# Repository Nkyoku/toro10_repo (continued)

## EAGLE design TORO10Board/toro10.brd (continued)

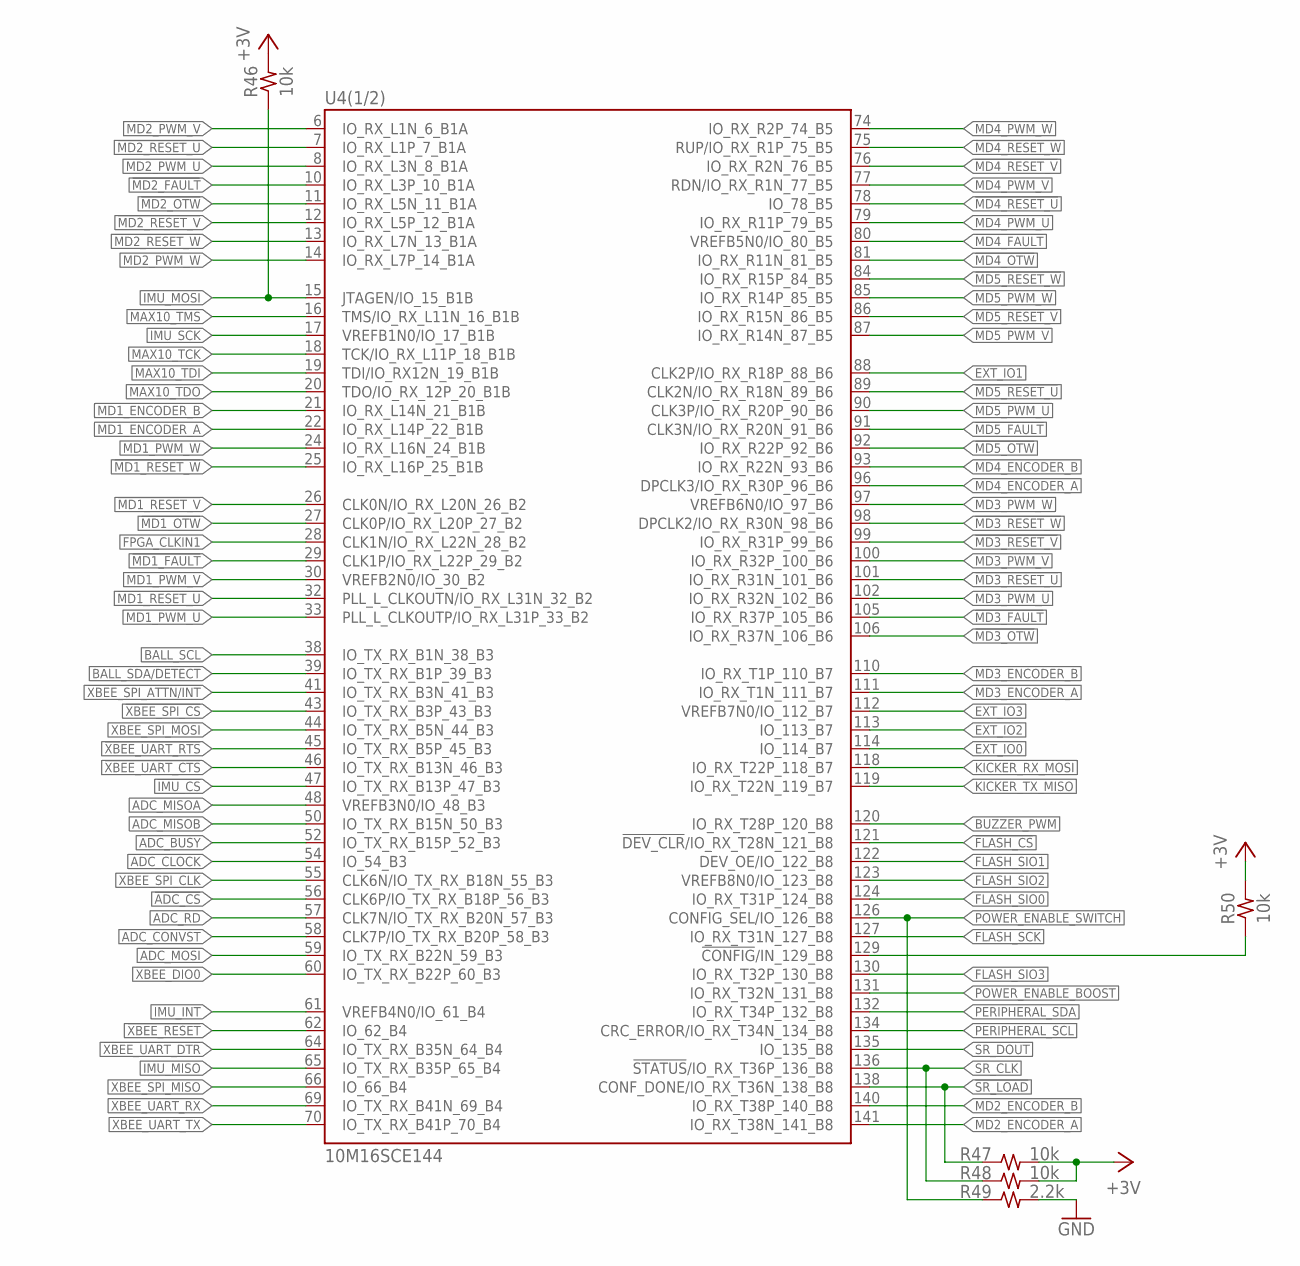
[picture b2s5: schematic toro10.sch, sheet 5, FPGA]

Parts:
R46, R47, R48, R50: 10k; 1608
R49: 2.2k; 1608
U4: 10M16SCE144; QFP144-0.5-PAD

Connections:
!ADC_CS: U4.56 (CLK6P/IO_TX_RX_B18P_56_B3); also elsewhere on the board
!FLASH_CS: U4.121 (!DEV_CLR!/IO_RX_T28N_121_B8); also elsewhere on the board
!IMU_CS: U4.47 (IO_TX_RX_B13P_47_B3); also elsewhere on the board
!MAX10_CONFIG: R50.1, U4.129 (!CONFIG!/IN_129_B8)
!MD1_FAULT: U4.29 (CLK1P/IO_RX_L22P_29_B2); also elsewhere on the board
!MD1_OTW: U4.27 (CLK0P/IO_RX_L20P_27_B2); also elsewhere on the board
!MD1_RESET_U: U4.32 (PLL_L_CLKOUTN/IO_RX_L31N_32_B2); also elsewhere on the board
!MD1_RESET_V: U4.26 (CLK0N/IO_RX_L20N_26_B2); also elsewhere on the board
!MD1_RESET_W: U4.25 (IO_RX_L16P_25_B1B); also elsewhere on the board
!MD2_FAULT: U4.10 (IO_RX_L3P_10_B1A); also elsewhere on the board
!MD2_OTW: U4.11 (IO_RX_L5N_11_B1A); also elsewhere on the board
!MD2_RESET_U: U4.7 (IO_RX_L1P_7_B1A); also elsewhere on the board
!MD2_RESET_V: U4.12 (IO_RX_L5P_12_B1A); also elsewhere on the board
!MD2_RESET_W: U4.13 (IO_RX_L7N_13_B1A); also elsewhere on the board
!MD3_FAULT: U4.105 (IO_RX_R37P_105_B6); also elsewhere on the board
!MD3_OTW: U4.106 (IO_RX_R37N_106_B6); also elsewhere on the board
!MD3_RESET_U: U4.101 (IO_RX_R31N_101_B6); also elsewhere on the board
!MD3_RESET_V: U4.99 (IO_RX_R31P_99_B6); also elsewhere on the board
!MD3_RESET_W: U4.98 (DPCLK2/IO_RX_R30N_98_B6); also elsewhere on the board
!MD4_FAULT: U4.80 (VREFB5N0/IO_80_B5); also elsewhere on the board
!MD4_OTW: U4.81 (IO_RX_R11N_81_B5); also elsewhere on the board
!MD4_RESET_U: U4.78 (IO_78_B5); also elsewhere on the board
!MD4_RESET_V: U4.76 (IO_RX_R2N_76_B5); also elsewhere on the board
!MD4_RESET_W: U4.75 (RUP/IO_RX_R1P_75_B5); also elsewhere on the board
!MD5_FAULT: U4.91 (CLK3N/IO_RX_R20N_91_B6); also elsewhere on the board
!MD5_OTW: U4.92 (IO_RX_R22P_92_B6); also elsewhere on the board
!MD5_RESET_U: U4.89 (CLK2N/IO_RX_R18N_89_B6); also elsewhere on the board
!MD5_RESET_V: U4.86 (IO_RX_R15N_86_B5); also elsewhere on the board
!MD5_RESET_W: U4.84 (IO_RX_R15P_84_B5); also elsewhere on the board
!SR_LOAD: R47.1, U4.138 (CONF_DONE/IO_RX_T36N_138_B8); also elsewhere on the board
!XBEE_RESET: U4.62 (IO_62_B4); also elsewhere on the board
!XBEE_SPI_ATTN/INT: U4.41 (IO_TX_RX_B3N_41_B3); also elsewhere on the board
!XBEE_SPI_CS: U4.43 (IO_TX_RX_B3P_43_B3); also elsewhere on the board
!XBEE_UART_CTS: U4.46 (IO_TX_RX_B13N_46_B3); also elsewhere on the board
!XBEE_UART_DTR: U4.64 (IO_TX_RX_B35N_64_B4); also elsewhere on the board
!XBEE_UART_RTS: U4.45 (IO_TX_RX_B5P_45_B3); also elsewhere on the board
+3V: R46.2, R47.2, R48.2, R50.2; also elsewhere on the board
ADC_BUSY: U4.52 (IO_TX_RX_B15P_52_B3); also elsewhere on the board
ADC_CLOCK: U4.54 (IO_54_B3); also elsewhere on the board
ADC_CONVST: U4.58 (CLK7P/IO_TX_RX_B20P_58_B3); also elsewhere on the board
ADC_MISOA: U4.48 (VREFB3N0/IO_48_B3); also elsewhere on the board
ADC_MISOB: U4.50 (IO_TX_RX_B15N_50_B3); also elsewhere on the board
ADC_MOSI: U4.59 (IO_TX_RX_B22N_59_B3); also elsewhere on the board
ADC_RD: U4.57 (CLK7N/IO_TX_RX_B20N_57_B3); also elsewhere on the board
BALL_SCL: U4.38 (IO_TX_RX_B1N_38_B3); also elsewhere on the board
BALL_SDA/DETECT: U4.39 (IO_TX_RX_B1P_39_B3); also elsewhere on the board
BUZZER_PWM: U4.120 (IO_RX_T28P_120_B8); also elsewhere on the board
EXT_IO0: U4.114 (IO_114_B7); also elsewhere on the board
EXT_IO1: U4.88 (CLK2P/IO_RX_R18P_88_B6); also elsewhere on the board
EXT_IO2: U4.113 (IO_113_B7); also elsewhere on the board
EXT_IO3: U4.112 (VREFB7N0/IO_112_B7); also elsewhere on the board
FLASH_SCK: U4.127 (IO_RX_T31N_127_B8); also elsewhere on the board
FLASH_SIO0: U4.124 (IO_RX_T31P_124_B8); also elsewhere on the board
FLASH_SIO1: U4.122 (DEV_OE/IO_122_B8); also elsewhere on the board
FLASH_SIO2: U4.123 (VREFB8N0/IO_123_B8); also elsewhere on the board
FLASH_SIO3: U4.130 (IO_RX_T32P_130_B8); also elsewhere on the board
FPGA_CLKIN1: U4.28 (CLK1N/IO_RX_L22N_28_B2); also elsewhere on the board
GND: R49.2; also elsewhere on the board
IMU_INT: U4.61 (VREFB4N0/IO_61_B4); also elsewhere on the board
IMU_MISO: U4.65 (IO_TX_RX_B35P_65_B4); also elsewhere on the board
IMU_MOSI: R46.1, U4.15 (JTAGEN/IO_15_B1B); also elsewhere on the board
IMU_SCK: U4.17 (VREFB1N0/IO_17_B1B); also elsewhere on the board
KICKER_RX_MOSI: U4.118 (IO_RX_T22P_118_B7); also elsewhere on the board
KICKER_TX_MISO: U4.119 (IO_RX_T22N_119_B7); also elsewhere on the board
MAX10_TCK: U4.18 (TCK/IO_RX_L11P_18_B1B); also elsewhere on the board
MAX10_TDI: U4.19 (TDI/IO_RX12N_19_B1B); also elsewhere on the board
MAX10_TDO: U4.20 (TDO/IO_RX_12P_20_B1B); also elsewhere on the board
MAX10_TMS: U4.16 (TMS/IO_RX_L11N_16_B1B); also elsewhere on the board
MD1_ENCODER_A: U4.22 (IO_RX_L14P_22_B1B); also elsewhere on the board
MD1_ENCODER_B: U4.21 (IO_RX_L14N_21_B1B); also elsewhere on the board
MD1_PWM_U: U4.33 (PLL_L_CLKOUTP/IO_RX_L31P_33_B2); also elsewhere on the board
MD1_PWM_V: U4.30 (VREFB2N0/IO_30_B2); also elsewhere on the board
MD1_PWM_W: U4.24 (IO_RX_L16N_24_B1B); also elsewhere on the board
MD2_ENCODER_A: U4.141 (IO_RX_T38N_141_B8); also elsewhere on the board
MD2_ENCODER_B: U4.140 (IO_RX_T38P_140_B8); also elsewhere on the board
MD2_PWM_U: U4.8 (IO_RX_L3N_8_B1A); also elsewhere on the board
MD2_PWM_V: U4.6 (IO_RX_L1N_6_B1A); also elsewhere on the board
MD2_PWM_W: U4.14 (IO_RX_L7P_14_B1A); also elsewhere on the board
MD3_ENCODER_A: U4.111 (IO_RX_T1N_111_B7); also elsewhere on the board
MD3_ENCODER_B: U4.110 (IO_RX_T1P_110_B7); also elsewhere on the board
MD3_PWM_U: U4.102 (IO_RX_R32N_102_B6); also elsewhere on the board
MD3_PWM_V: U4.100 (IO_RX_R32P_100_B6); also elsewhere on the board
MD3_PWM_W: U4.97 (VREFB6N0/IO_97_B6); also elsewhere on the board
MD4_ENCODER_A: U4.96 (DPCLK3/IO_RX_R30P_96_B6); also elsewhere on the board
MD4_ENCODER_B: U4.93 (IO_RX_R22N_93_B6); also elsewhere on the board
MD4_PWM_U: U4.79 (IO_RX_R11P_79_B5); also elsewhere on the board
MD4_PWM_V: U4.77 (RDN/IO_RX_R1N_77_B5); also elsewhere on the board
MD4_PWM_W: U4.74 (IO_RX_R2P_74_B5); also elsewhere on the board
MD5_PWM_U: U4.90 (CLK3P/IO_RX_R20P_90_B6); also elsewhere on the board
MD5_PWM_V: U4.87 (IO_RX_R14N_87_B5); also elsewhere on the board
MD5_PWM_W: U4.85 (IO_RX_R14P_85_B5); also elsewhere on the board
PERIPHERAL_SCL: U4.134 (CRC_ERROR/IO_RX_T34N_134_B8); also elsewhere on the board
PERIPHERAL_SDA: U4.132 (IO_RX_T34P_132_B8); also elsewhere on the board
POWER_ENABLE_BOOST: U4.131 (IO_RX_T32N_131_B8); also elsewhere on the board
POWER_ENABLE_SWITCH: R49.1, U4.126 (CONFIG_SEL/IO_126_B8); also elsewhere on the board
SR_CLK: R48.1, U4.136 (!STATUS!/IO_RX_T36P_136_B8); also elsewhere on the board
SR_DOUT: U4.135 (IO_135_B8); also elsewhere on the board
XBEE_DIO0: U4.60 (IO_TX_RX_B22P_60_B3); also elsewhere on the board
XBEE_SPI_CLK: U4.55 (CLK6N/IO_TX_RX_B18N_55_B3); also elsewhere on the board
XBEE_SPI_MISO: U4.66 (IO_66_B4); also elsewhere on the board
XBEE_SPI_MOSI: U4.44 (IO_TX_RX_B5N_44_B3); also elsewhere on the board
XBEE_UART_RX: U4.69 (IO_TX_RX_B41N_69_B4); also elsewhere on the board
XBEE_UART_TX: U4.70 (IO_TX_RX_B41P_70_B4); also elsewhere on the board

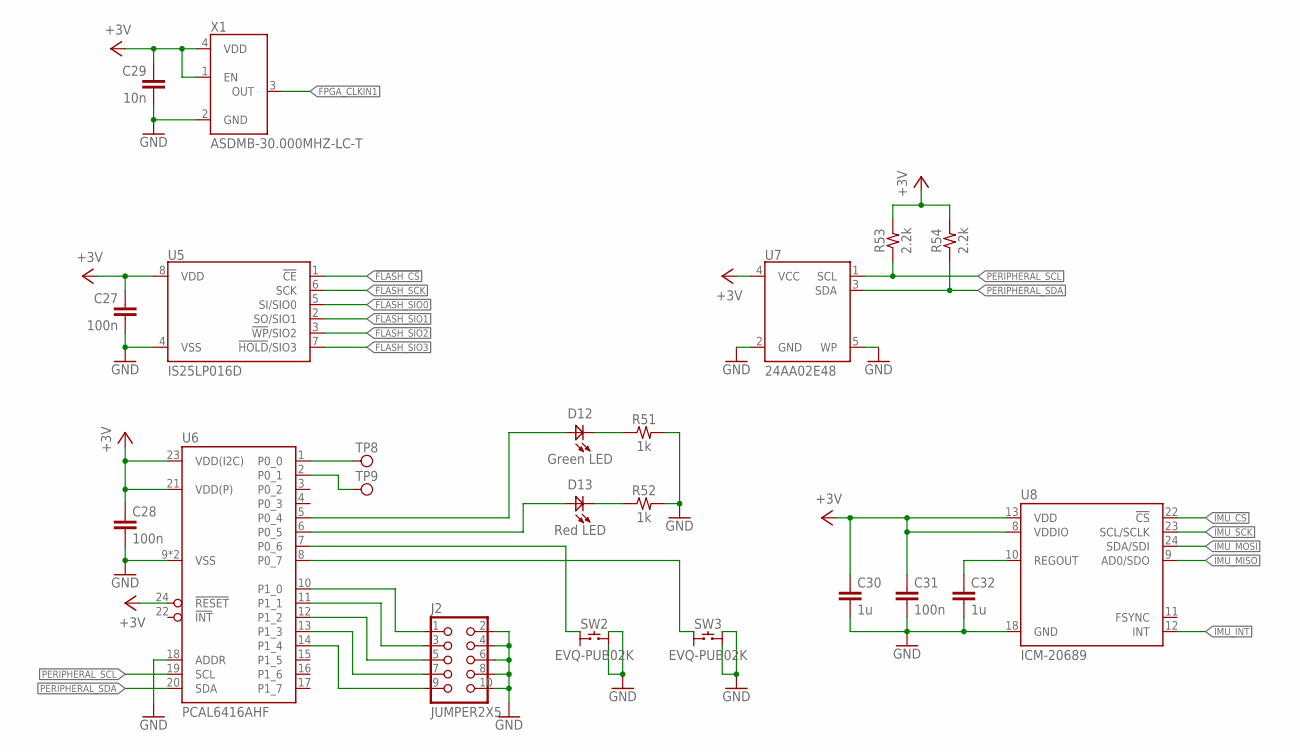
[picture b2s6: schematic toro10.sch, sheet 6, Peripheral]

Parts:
C27, C28, C31: 100n; 1608
C29: 10n; 1608
C30, C32: 1u; 1608
D12: Green LED; 1608D
D13: Red LED; 1608D
J2: JUMPER2X5; PIN2X5
R51, R52: 1k; 1608
R53, R54: 2.2k; 1608
SW2, SW3: EVQ-PUB02K; EVQ-PU_BK
TP8, TP9: TESTPAD-SMT
U5: IS25LP016D; SOP8
U6: PCAL6416AHF; QFN24-0.5
U7: 24AA02E48; SOT23-5
U8: ICM-20689; QFN24-0.5-INVEN
X1: ASDMB-30.000MHZ-LC-T; OSC2520

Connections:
!FLASH_CS: U5.1 (!CE); also elsewhere on the board
!IMU_CS: U8.22 (!CS); also elsewhere on the board
+3V: C27.1, C28.1, C29.1, C30.1, C31.1, R53.2, R54.2, U5.8 (VDD), U6.21 (VDD(P)), U6.23 (VDD(I2C)), U6.24 (!RESET), U7.4 (VCC), U8.8 (VDDIO), U8.13 (VDD), X1.1 (EN), X1.4 (VDD); also elsewhere on the board
FLASH_SCK: U5.6 (SCK); also elsewhere on the board
FLASH_SIO0: U5.5 (SI/SIO0); also elsewhere on the board
FLASH_SIO1: U5.2 (SO/SIO1); also elsewhere on the board
FLASH_SIO2: U5.3 (!WP!/SIO2); also elsewhere on the board
FLASH_SIO3: U5.7 (!HOLD!/SIO3); also elsewhere on the board
FPGA_CLKIN1: X1.3 (OUT); also elsewhere on the board
GND: C27.2, C28.2, C29.2, C30.2, C31.2, C32.2, J2.2, J2.4, J2.6, J2.8, J2.10, R51.2, R52.2, SW2.A1, SW2.A2, SW3.A1, SW3.A2, U5.4 (VSS), U6.9 (VSS), U6.18 (ADDR), U6.PAD (VSS), U7.2 (GND), U7.5 (WP), U8.18 (GND), X1.2 (GND); also elsewhere on the board
IMU_INT: U8.12 (INT); also elsewhere on the board
IMU_MISO: U8.9 (AD0/SDO); also elsewhere on the board
IMU_MOSI: U8.24 (SDA/SDI); also elsewhere on the board
IMU_SCK: U8.23 (SCL/SCLK); also elsewhere on the board
unnamed: D12.A, U6.5 (P0_4)
unnamed: D13.A, U6.6 (P0_5)
unnamed: J2.1, U6.10 (P1_0)
unnamed: J2.3, U6.11 (P1_1)
unnamed: J2.5, U6.12 (P1_2)
unnamed: J2.7, U6.13 (P1_3)
unnamed: J2.9, U6.14 (P1_4)
unnamed: SW3.B1, U6.8 (P0_7)
unnamed: SW2.B1, U6.7 (P0_6)
unnamed: TP8.1, U6.1 (P0_0)
unnamed: TP9.1, U6.2 (P0_1)
unnamed: D12.K, R51.1
unnamed: D13.K, R52.1
unnamed: C32.1, U8.10 (REGOUT)
PERIPHERAL_SCL: R53.1, U6.19 (SCL), U7.1 (SCL); also elsewhere on the board
PERIPHERAL_SDA: R54.1, U6.20 (SDA), U7.3 (SDA); also elsewhere on the board

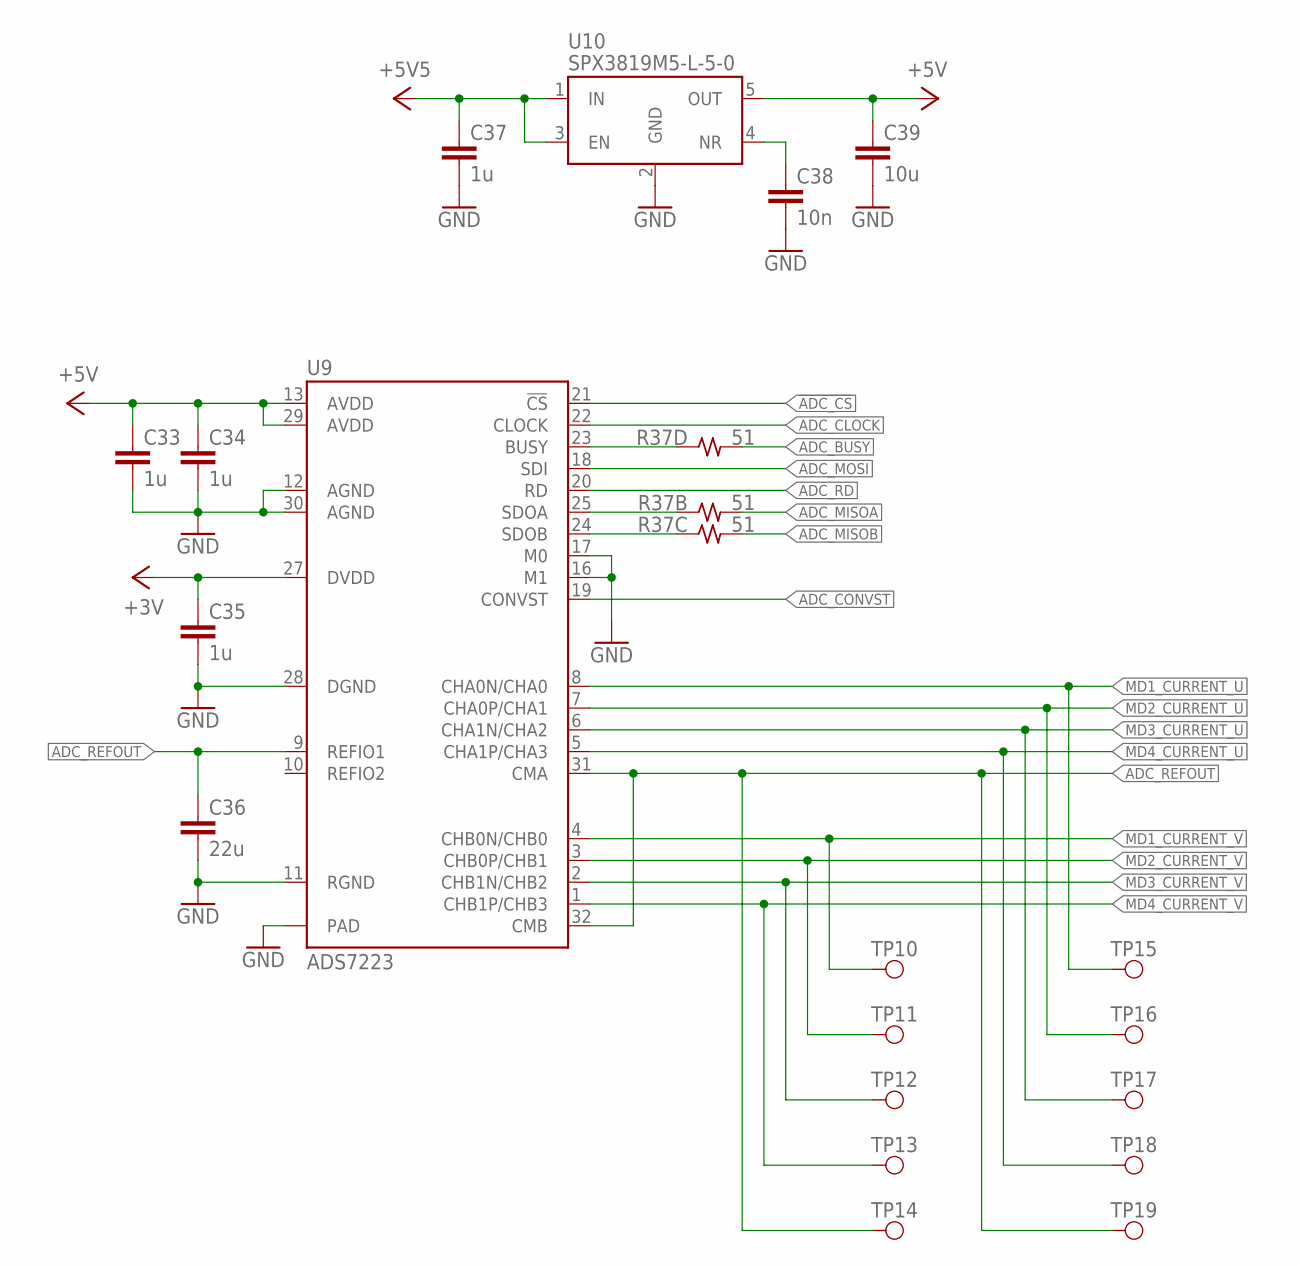
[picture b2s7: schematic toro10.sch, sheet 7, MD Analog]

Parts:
C33, C34, C35, C37: 1u; 1608
C36: 22u; 2012
C38: 10n; 1608
C39: 10u; 2012
R37: 51; 1608-4A
TP10, TP11, TP12, TP13, TP14, TP15, TP16, TP17, TP18, TP19: TESTPAD-TH
U9: ADS7223; QFN32-0.5
U10: SPX3819M5-L-5-0; SOT23-5

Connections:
!ADC_CS: U9.21 (!CS); also elsewhere on the board
+3V: C35.1, U9.27 (DVDD); also elsewhere on the board
+5V: C33.1, C34.1, C39.1, U9.13 (AVDD), U9.29 (AVDD), U10.5 (OUT); also elsewhere on the board
+5V5: C37.1, U10.1 (IN), U10.3 (EN); also elsewhere on the board
ADC_BUSY: R37.D2 (2); also elsewhere on the board
ADC_CLOCK: U9.22 (CLOCK); also elsewhere on the board
ADC_CONVST: U9.19 (CONVST); also elsewhere on the board
ADC_MISOA: R37.B2 (2); also elsewhere on the board
ADC_MISOB: R37.C2 (2); also elsewhere on the board
ADC_MOSI: U9.18 (SDI); also elsewhere on the board
ADC_RD: U9.20 (RD); also elsewhere on the board
ADC_REFOUT: C36.1, TP14.1, TP19.1, U9.9 (REFIO1), U9.31 (CMA), U9.32 (CMB); also elsewhere on the board
GND: C33.2, C34.2, C35.2, C36.2, C37.2, C38.2, C39.2, U9.11 (RGND), U9.12 (AGND), U9.16 (M1), U9.17 (M0), U9.28 (DGND), U9.30 (AGND), U9.PAD, U10.2 (GND); also elsewhere on the board
MD1_CURRENT_U: TP15.1, U9.8 (CHA0N/CHA0); also elsewhere on the board
MD1_CURRENT_V: TP10.1, U9.4 (CHB0N/CHB0); also elsewhere on the board
MD2_CURRENT_U: TP16.1, U9.7 (CHA0P/CHA1); also elsewhere on the board
MD2_CURRENT_V: TP11.1, U9.3 (CHB0P/CHB1); also elsewhere on the board
MD3_CURRENT_U: TP17.1, U9.6 (CHA1N/CHA2); also elsewhere on the board
MD3_CURRENT_V: TP12.1, U9.2 (CHB1N/CHB2); also elsewhere on the board
MD4_CURRENT_U: TP18.1, U9.5 (CHA1P/CHA3); also elsewhere on the board
MD4_CURRENT_V: TP13.1, U9.1 (CHB1P/CHB3); also elsewhere on the board
unnamed: C38.1, U10.4 (NR)
unnamed: R37.D1 (1), U9.23 (BUSY)
unnamed: R37.B1 (1), U9.25 (SDOA)
unnamed: R37.C1 (1), U9.24 (SDOB)

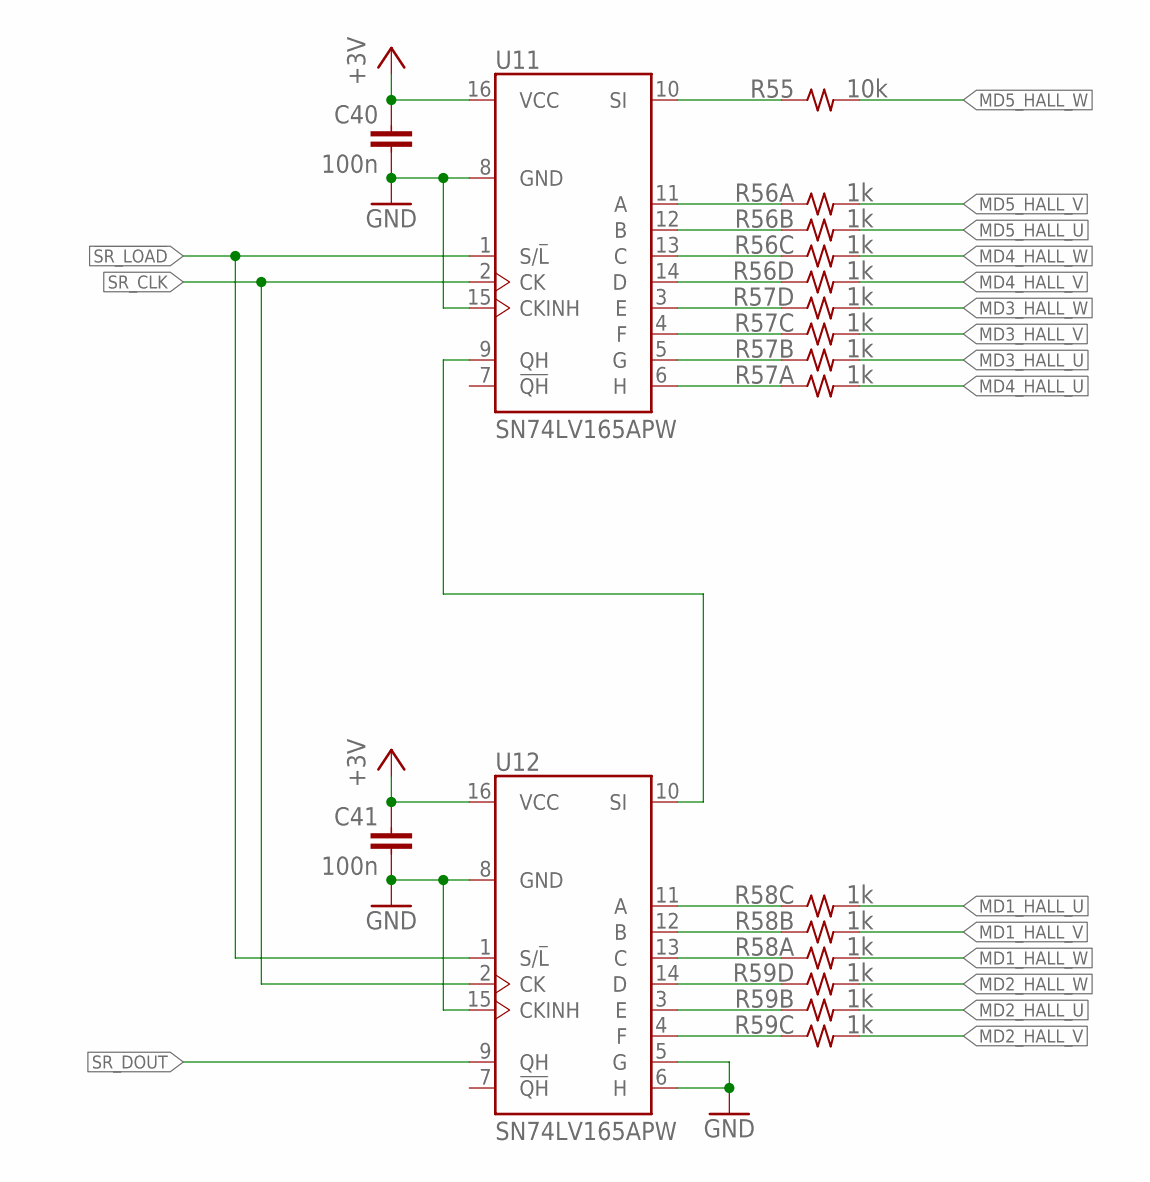
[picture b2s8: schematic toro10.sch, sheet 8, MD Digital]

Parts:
C40, C41: 100n; 1608
R55: 10k; 1608
R56, R57, R58, R59: 1k; 1608-4A
U11, U12: SN74LV165APW; TSSOP16

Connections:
!SR_LOAD: U11.1 (S/!L), U12.1 (S/!L); also elsewhere on the board
+3V: C40.1, C41.1, U11.16 (VCC), U12.16 (VCC); also elsewhere on the board
GND: C40.2, C41.2, U11.8 (GND), U11.15 (CKINH), U12.5 (G), U12.6 (H), U12.8 (GND), U12.15 (CKINH); also elsewhere on the board
MD1_HALL_U: R58.C2 (2); also elsewhere on the board
MD1_HALL_V: R58.B2 (2); also elsewhere on the board
MD1_HALL_W: R58.A2 (2); also elsewhere on the board
MD2_HALL_U: R59.B2 (2); also elsewhere on the board
MD2_HALL_V: R59.C2 (2); also elsewhere on the board
MD2_HALL_W: R59.D2 (2); also elsewhere on the board
MD3_HALL_U: R57.B2 (2); also elsewhere on the board
MD3_HALL_V: R57.C2 (2); also elsewhere on the board
MD3_HALL_W: R57.D2 (2); also elsewhere on the board
MD4_HALL_U: R57.A2 (2); also elsewhere on the board
MD4_HALL_V: R56.D2 (2); also elsewhere on the board
MD4_HALL_W: R56.C2 (2); also elsewhere on the board
MD5_HALL_U: R56.B2 (2); also elsewhere on the board
MD5_HALL_V: R56.A2 (2); also elsewhere on the board
MD5_HALL_W: R55.2; also elsewhere on the board
unnamed: R59.B1 (1), U12.3 (E)
unnamed: R59.C1 (1), U12.4 (F)
unnamed: R59.D1 (1), U12.14 (D)
unnamed: R58.A1 (1), U12.13 (C)
unnamed: R58.B1 (1), U12.12 (B)
unnamed: R58.C1 (1), U12.11 (A)
unnamed: U11.9 (QH), U12.10 (SI)
unnamed: R57.D1 (1), U11.3 (E)
unnamed: R57.C1 (1), U11.4 (F)
unnamed: R57.B1 (1), U11.5 (G)
unnamed: R57.A1 (1), U11.6 (H)
unnamed: R56.D1 (1), U11.14 (D)
unnamed: R56.C1 (1), U11.13 (C)
unnamed: R56.B1 (1), U11.12 (B)
unnamed: R56.A1 (1), U11.11 (A)
unnamed: R55.1, U11.10 (SI)
SR_CLK: U11.2 (CK), U12.2 (CK); also elsewhere on the board
SR_DOUT: U12.9 (QH); also elsewhere on the board

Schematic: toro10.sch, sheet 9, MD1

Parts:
C42, C43, C44, C45: 1u; 1608
C46, C47, C48, C49, C50, C51, C52, C53, C55: 100n; 1608
C54, C56: DNC; 1608
CN12: 43045-0800
CN13: 53426-0410; 53426-04
D14, D15: GS1010FL; SOD123
F2: MICROSMD010-2; 3225
R60: 1; 1608
R61: 22k; 1608
R62, R64, R65, R67: 0; 1608
R63, R66: 2m; 3216
R68: 100k; 1608-4A
R69, R70: 1k; 1608
U13: DRV8332; HSSOP36
U14, U15: INA240A2; TSSOP8

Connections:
!MD1_FAULT: U13.3 (!FAULT); also elsewhere on the board
!MD1_OTW: U13.2 (!OTW); also elsewhere on the board
!MD1_RESET_U: U13.5 (!RESET_A); also elsewhere on the board
!MD1_RESET_V: U13.14 (!RESET_B); also elsewhere on the board
!MD1_RESET_W: U13.15 (!RESET_C); also elsewhere on the board
+5V: C47.1, C48.1, U14.5 (VS), U15.5 (VS); also elsewhere on the board
+5V5: F2.1; also elsewhere on the board
+12V: C42.1, C43.1, C44.1, C45.1, U13.1 (GVDD_B), U13.17 (VDD), U13.18 (GVDD_C), U13.19 (GVDD_C), U13.36 (GVDD_A); also elsewhere on the board
+48V: C52.1, C53.1, C55.1, U13.21 (PVDD_C), U13.29 (PVDD_B), U13.34 (PVDD_A); also elsewhere on the board
ADC_REFOUT: U14.6 (REF2), U14.7 (REF1), U15.6 (REF2), U15.7 (REF1); also elsewhere on the board
GND: C42.2, C43.2, C44.2, C45.2, C47.2, C48.2, C52.2, C53.2, C55.2, CN12.1, CN13.2, R60.1, U13.8 (GND), U13.23 (GND_C), U13.24 (GND), U13.25 (GND), U13.31 (GND_B), U13.32 (GND_A), U14.1 (NC), U14.4 (GND), U15.1 (NC), U15.4 (GND); also elsewhere on the board
MD1_CURRENT_U: U14.8 (OUT); also elsewhere on the board
MD1_CURRENT_V: U15.8 (OUT); also elsewhere on the board
MD1_ENCODER_A: R70.1; also elsewhere on the board
MD1_ENCODER_B: R69.1; also elsewhere on the board
MD1_HALL_U: CN12.2, R68.C1 (1); also elsewhere on the board
MD1_HALL_V: CN12.3, R68.B1 (1); also elsewhere on the board
MD1_HALL_W: CN12.4, R68.A1 (1); also elsewhere on the board
MD1_PWM_U: U13.4 (PWM_A); also elsewhere on the board
MD1_PWM_V: U13.6 (PWM_B); also elsewhere on the board
MD1_PWM_W: U13.16 (PWM_C); also elsewhere on the board
unnamed: C49.2, R62.2, R63.1, U13.33 (OUT_A)
unnamed: CN12.5, R63.2, R64.2
unnamed: R61.2, U13.7 (OC_ADJ)
unnamed: C46.2, U13.10 (VREG), U13.11 (M3)
unnamed: C46.1, R60.2, R61.1, U13.9 (AGND), U13.12 (M2), U13.13 (M1)
unnamed: C51.2, CN12.7, U13.22 (OUT_C)
unnamed: C56.1, R65.1, U15.2 (IN+)
unnamed: C54.1, R62.1, U14.2 (IN+)
unnamed: C49.1, U13.35 (BST_A)
unnamed: C50.1, U13.28 (BST_B)
unnamed: C51.1, U13.20 (BST_C)
unnamed: CN13.1, R69.2
unnamed: C54.2, R64.1, U14.3 (IN-)
unnamed: C56.2, R67.1, U15.3 (IN-)
unnamed: D14.A, D15.A, F2.2
unnamed: CN13.4, D15.K
unnamed: CN12.8, D14.K, R68.A2 (2), R68.B2 (2), R68.C2 (2)
unnamed: CN13.3, R70.2
unnamed: C50.2, R65.2, R66.1, U13.30 (OUT_B)
unnamed: CN12.6, R66.2, R67.2

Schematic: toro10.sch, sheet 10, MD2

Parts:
C57, C58, C59, C60: 1u; 1608
C61, C62, C63, C64, C65, C66, C68: 100n; 1608
C67, C69: DNC; 1608
CN14: 43045-0800
CN15: 53426-0410; 53426-04
D16, D17: GS1010FL; SOD123
F3: MICROSMD010-2; 3225
R71: 1; 1608
R72: 22k; 1608
R73, R75, R76, R78: 0; 1608
R74, R77: 2m; 3216
R79: 100k; 1608-4A
R80, R81: 1k; 1608
U16: DRV8332; HSSOP36
U17, U18: INA240A2; TSSOP8

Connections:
!MD2_FAULT: U16.3 (!FAULT); also elsewhere on the board
!MD2_OTW: U16.2 (!OTW); also elsewhere on the board
!MD2_RESET_U: U16.5 (!RESET_A); also elsewhere on the board
!MD2_RESET_V: U16.14 (!RESET_B); also elsewhere on the board
!MD2_RESET_W: U16.15 (!RESET_C); also elsewhere on the board
+5V: U17.5 (VS), U18.5 (VS); also elsewhere on the board
+5V5: F3.1; also elsewhere on the board
+12V: C57.1, C58.1, C59.1, C60.1, U16.1 (GVDD_B), U16.17 (VDD), U16.18 (GVDD_C), U16.19 (GVDD_C), U16.36 (GVDD_A); also elsewhere on the board
+48V: C65.1, C66.1, C68.1, U16.21 (PVDD_C), U16.29 (PVDD_B), U16.34 (PVDD_A); also elsewhere on the board
ADC_REFOUT: U17.6 (REF2), U17.7 (REF1), U18.6 (REF2), U18.7 (REF1); also elsewhere on the board
GND: C57.2, C58.2, C59.2, C60.2, C65.2, C66.2, C68.2, CN14.1, CN15.2, R71.1, U16.8 (GND), U16.23 (GND_C), U16.24 (GND), U16.25 (GND), U16.31 (GND_B), U16.32 (GND_A), U17.1 (NC), U17.4 (GND), U18.1 (NC), U18.4 (GND); also elsewhere on the board
MD2_CURRENT_U: U17.8 (OUT); also elsewhere on the board
MD2_CURRENT_V: U18.8 (OUT); also elsewhere on the board
MD2_ENCODER_A: R81.1; also elsewhere on the board
MD2_ENCODER_B: R80.1; also elsewhere on the board
MD2_HALL_U: CN14.2, R79.D1 (1); also elsewhere on the board
MD2_HALL_V: CN14.3, R79.C1 (1); also elsewhere on the board
MD2_HALL_W: CN14.4, R79.B1 (1); also elsewhere on the board
MD2_PWM_U: U16.4 (PWM_A); also elsewhere on the board
MD2_PWM_V: U16.6 (PWM_B); also elsewhere on the board
MD2_PWM_W: U16.16 (PWM_C); also elsewhere on the board
unnamed: R72.2, U16.7 (OC_ADJ)
unnamed: C61.2, U16.10 (VREG), U16.11 (M3)
unnamed: C61.1, R71.2, R72.1, U16.9 (AGND), U16.12 (M2), U16.13 (M1)
unnamed: C64.2, CN14.7, U16.22 (OUT_C)
unnamed: C69.1, R76.1, U18.2 (IN+)
unnamed: C67.1, R73.1, U17.2 (IN+)
unnamed: C62.1, U16.35 (BST_A)
unnamed: C63.1, U16.28 (BST_B)
unnamed: C64.1, U16.20 (BST_C)
unnamed: CN14.8, D16.K, R79.B2 (2), R79.C2 (2), R79.D2 (2)
unnamed: C67.2, R75.1, U17.3 (IN-)
unnamed: C69.2, R78.1, U18.3 (IN-)
unnamed: CN15.4, D17.K
unnamed: D16.A, D17.A, F3.2
unnamed: C62.2, R73.2, R74.1, U16.33 (OUT_A)
unnamed: CN14.5, R74.2, R75.2
unnamed: C63.2, R76.2, R77.1, U16.30 (OUT_B)
unnamed: CN14.6, R77.2, R78.2
unnamed: CN15.1, R80.2
unnamed: CN15.3, R81.2

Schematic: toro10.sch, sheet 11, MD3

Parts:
C70, C71, C72, C73: 1u; 1608
C74, C75, C76, C77, C78, C79, C80, C81, C83: 100n; 1608
C82, C84: DNC; 1608
CN16: 43045-0800
CN17: 53426-0410; 53426-04
D18, D19: GS1010FL; SOD123
F4: MICROSMD010-2; 3225
R82: 1; 1608
R83: 22k; 1608
R84, R86, R87, R89: 0; 1608
R85, R88: 2m; 3216
R90: 100k; 1608-4A
R91, R92: 1k; 1608
U19: DRV8332; HSSOP36
U20, U21: INA240A2; TSSOP8

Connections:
!MD3_FAULT: U19.3 (!FAULT); also elsewhere on the board
!MD3_OTW: U19.2 (!OTW); also elsewhere on the board
!MD3_RESET_U: U19.5 (!RESET_A); also elsewhere on the board
!MD3_RESET_V: U19.14 (!RESET_B); also elsewhere on the board
!MD3_RESET_W: U19.15 (!RESET_C); also elsewhere on the board
+5V: C75.1, C76.1, U20.5 (VS), U21.5 (VS); also elsewhere on the board
+5V5: F4.1; also elsewhere on the board
+12V: C70.1, C71.1, C72.1, C73.1, U19.1 (GVDD_B), U19.17 (VDD), U19.18 (GVDD_C), U19.19 (GVDD_C), U19.36 (GVDD_A); also elsewhere on the board
+48V: C80.1, C81.1, C83.1, U19.21 (PVDD_C), U19.29 (PVDD_B), U19.34 (PVDD_A); also elsewhere on the board
ADC_REFOUT: U20.6 (REF2), U20.7 (REF1), U21.6 (REF2), U21.7 (REF1); also elsewhere on the board
GND: C70.2, C71.2, C72.2, C73.2, C75.2, C76.2, C80.2, C81.2, C83.2, CN16.1, CN17.2, R82.1, U19.8 (GND), U19.23 (GND_C), U19.24 (GND), U19.25 (GND), U19.31 (GND_B), U19.32 (GND_A), U20.1 (NC), U20.4 (GND), U21.1 (NC), U21.4 (GND); also elsewhere on the board
MD3_CURRENT_U: U20.8 (OUT); also elsewhere on the board
MD3_CURRENT_V: U21.8 (OUT); also elsewhere on the board
MD3_ENCODER_A: R92.1; also elsewhere on the board
MD3_ENCODER_B: R91.1; also elsewhere on the board
MD3_HALL_U: CN16.2, R90.C1 (1); also elsewhere on the board
MD3_HALL_V: CN16.3, R90.B1 (1); also elsewhere on the board
MD3_HALL_W: CN16.4, R90.A1 (1); also elsewhere on the board
MD3_PWM_U: U19.4 (PWM_A); also elsewhere on the board
MD3_PWM_V: U19.6 (PWM_B); also elsewhere on the board
MD3_PWM_W: U19.16 (PWM_C); also elsewhere on the board
unnamed: R83.2, U19.7 (OC_ADJ)
unnamed: C74.2, U19.10 (VREG), U19.11 (M3)
unnamed: C74.1, R82.2, R83.1, U19.9 (AGND), U19.12 (M2), U19.13 (M1)
unnamed: C79.2, CN16.7, U19.22 (OUT_C)
unnamed: C84.1, R87.1, U21.2 (IN+)
unnamed: C82.1, R84.1, U20.2 (IN+)
unnamed: C77.1, U19.35 (BST_A)
unnamed: C78.1, U19.28 (BST_B)
unnamed: C79.1, U19.20 (BST_C)
unnamed: CN16.8, D18.K, R90.A2 (2), R90.B2 (2), R90.C2 (2)
unnamed: C82.2, R86.1, U20.3 (IN-)
unnamed: C84.2, R89.1, U21.3 (IN-)
unnamed: CN17.4, D19.K
unnamed: D18.A, D19.A, F4.2
unnamed: C77.2, R84.2, R85.1, U19.33 (OUT_A)
unnamed: CN16.5, R85.2, R86.2
unnamed: C78.2, R87.2, R88.1, U19.30 (OUT_B)
unnamed: CN16.6, R88.2, R89.2
unnamed: CN17.1, R91.2
unnamed: CN17.3, R92.2

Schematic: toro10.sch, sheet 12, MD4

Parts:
C85, C86, C87, C88: 1u; 1608
C89, C90, C91, C92, C93, C94, C96: 100n; 1608
C95, C97: DNC; 1608
CN18: 43045-0800
CN19: 53426-0410; 53426-04
D20, D21: GS1010FL; SOD123
F5: MICROSMD010-2; 3225
R93: 1; 1608
R94: 22k; 1608
R95, R97, R98, R100: 0; 1608
R96, R99: 2m; 3216
R101: 100k; 1608-4A
R102, R103: 1k; 1608
U22: DRV8332; HSSOP36
U23, U24: INA240A2; TSSOP8

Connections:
!MD4_FAULT: U22.3 (!FAULT); also elsewhere on the board
!MD4_OTW: U22.2 (!OTW); also elsewhere on the board
!MD4_RESET_U: U22.5 (!RESET_A); also elsewhere on the board
!MD4_RESET_V: U22.14 (!RESET_B); also elsewhere on the board
!MD4_RESET_W: U22.15 (!RESET_C); also elsewhere on the board
+5V: U23.5 (VS), U24.5 (VS); also elsewhere on the board
+5V5: F5.1; also elsewhere on the board
+12V: C85.1, C86.1, C87.1, C88.1, U22.1 (GVDD_B), U22.17 (VDD), U22.18 (GVDD_C), U22.19 (GVDD_C), U22.36 (GVDD_A); also elsewhere on the board
+48V: C93.1, C94.1, C96.1, U22.21 (PVDD_C), U22.29 (PVDD_B), U22.34 (PVDD_A); also elsewhere on the board
ADC_REFOUT: U23.6 (REF2), U23.7 (REF1), U24.6 (REF2), U24.7 (REF1); also elsewhere on the board
GND: C85.2, C86.2, C87.2, C88.2, C93.2, C94.2, C96.2, CN18.1, CN19.2, R93.1, U22.8 (GND), U22.23 (GND_C), U22.24 (GND), U22.25 (GND), U22.31 (GND_B), U22.32 (GND_A), U23.1 (NC), U23.4 (GND), U24.1 (NC), U24.4 (GND); also elsewhere on the board
MD4_CURRENT_U: U23.8 (OUT); also elsewhere on the board
MD4_CURRENT_V: U24.8 (OUT); also elsewhere on the board
MD4_ENCODER_A: R103.1; also elsewhere on the board
MD4_ENCODER_B: R102.1; also elsewhere on the board
MD4_HALL_U: CN18.2, R101.D1 (1); also elsewhere on the board
MD4_HALL_V: CN18.3, R101.C1 (1); also elsewhere on the board
MD4_HALL_W: CN18.4, R101.B1 (1); also elsewhere on the board
MD4_PWM_U: U22.4 (PWM_A); also elsewhere on the board
MD4_PWM_V: U22.6 (PWM_B); also elsewhere on the board
MD4_PWM_W: U22.16 (PWM_C); also elsewhere on the board
unnamed: R94.2, U22.7 (OC_ADJ)
unnamed: C89.2, U22.10 (VREG), U22.11 (M3)
unnamed: C89.1, R93.2, R94.1, U22.9 (AGND), U22.12 (M2), U22.13 (M1)
unnamed: C92.2, CN18.7, U22.22 (OUT_C)
unnamed: C97.1, R98.1, U24.2 (IN+)
unnamed: C95.1, R95.1, U23.2 (IN+)
unnamed: C90.1, U22.35 (BST_A)
unnamed: C91.1, U22.28 (BST_B)
unnamed: C92.1, U22.20 (BST_C)
unnamed: CN18.8, D20.K, R101.B2 (2), R101.C2 (2), R101.D2 (2)
unnamed: C95.2, R97.1, U23.3 (IN-)
unnamed: C97.2, R100.1, U24.3 (IN-)
unnamed: CN19.4, D21.K
unnamed: D20.A, D21.A, F5.2
unnamed: C90.2, R95.2, R96.1, U22.33 (OUT_A)
unnamed: CN18.5, R96.2, R97.2
unnamed: C91.2, R98.2, R99.1, U22.30 (OUT_B)
unnamed: CN18.6, R99.2, R100.2
unnamed: CN19.1, R102.2
unnamed: CN19.3, R103.2

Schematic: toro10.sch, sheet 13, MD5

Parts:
C98, C99, C100, C101: 1u; 1608
C102, C103, C104, C105, C106, C107, C108: 100n; 1608
CN20: PIN1X8
D22: GS1010FL; SOD123
F6: MICROSMD010-2; 3225
R104: 1; 1608
R105: 47k; 1608
R106: 100k; 1608-4A
U25: DRV8312; HTSSOP44

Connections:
!MD5_FAULT: U25.18 (!FAULT); also elsewhere on the board
!MD5_OTW: U25.21 (!OTW); also elsewhere on the board
!MD5_RESET_U: U25.16 (!RESET_A); also elsewhere on the board
!MD5_RESET_V: U25.7 (!RESET_B); also elsewhere on the board
!MD5_RESET_W: U25.6 (!RESET_C); also elsewhere on the board
+5V5: F6.1; also elsewhere on the board
+12V: C98.1, C99.1, C100.1, C101.1, U25.1 (GVDD_C), U25.2 (VDD), U25.22 (GVDD_B), U25.23 (GVDD_A), U25.44 (GVDD_C); also elsewhere on the board
+48V: C106.1, C107.1, C108.1, U25.26 (PVDD_A), U25.27 (PVDD_A), U25.32 (PVDD_B), U25.40 (PVDD_C), U25.41 (PVDD_C); also elsewhere on the board
GND: C98.2, C99.2, C100.2, C101.2, C106.2, C107.2, C108.2, CN20.5, R104.1, U25.13 (GND), U25.29 (GND_A), U25.30 (GND_B), U25.36 (GND), U25.37 (GND), U25.38 (GND_C), U25.PAD (GND); also elsewhere on the board
MD5_HALL_U: CN20.6, R106.C1 (1); also elsewhere on the board
MD5_HALL_V: CN20.7, R106.B1 (1); also elsewhere on the board
MD5_HALL_W: CN20.8, R106.A1 (1); also elsewhere on the board
MD5_PWM_U: U25.17 (PWM_A); also elsewhere on the board
MD5_PWM_V: U25.15 (PWM_B); also elsewhere on the board
MD5_PWM_W: U25.5 (PWM_C); also elsewhere on the board
unnamed: CN20.4, D22.K, R106.A2 (2), R106.B2 (2), R106.C2 (2)
unnamed: R105.2, U25.14 (OC_ADJ)
unnamed: D22.A, F6.2
unnamed: C102.2, U25.10 (M3), U25.11 (VREG)
unnamed: C102.1, R104.2, R105.1, U25.8 (M1), U25.9 (M2), U25.12 (AGND)
unnamed: C105.2, CN20.1, U25.39 (OUT_C)
unnamed: C104.2, CN20.2, U25.31 (OUT_B)
unnamed: C103.2, CN20.3, U25.28 (OUT_A)
unnamed: C103.1, U25.24 (BST_A)
unnamed: C104.1, U25.33 (BST_B)
unnamed: C105.1, U25.43 (BST_C)

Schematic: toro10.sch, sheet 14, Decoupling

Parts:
C109: 10u; 2012
C110, C111, C112, C113, C114, C115, C116, C117, C118, C119, C120, C121, C122, C123, C124, C125, C126, C127, C128, C129, C130, C131, C132, C133: 100n; 1608
FB1: BLM18PG471SN1D; 1608
U4: 10M16SCE144; QFP144-0.5-PAD

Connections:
+3V: C110.1, C111.1, C113.1, C114.1, C116.1, C117.1, C119.1, C120.1, C122.1, C123.1, C125.1, C126.1, C127.1, C128.1, C129.1, C130.1, C131.1, C132.1, C133.1, FB1.1, U4.1 (VCC_ONE), U4.9 (VCCIO1A), U4.23 (VCCIO1B), U4.31 (VCCIO2), U4.36 (VCC_ONE), U4.37 (VCC_ONE), U4.40 (VCCIO3), U4.49 (VCCIO3), U4.51 (VCC_ONE), U4.67 (VCCIO4), U4.72 (VCC_ONE), U4.73 (VCC_ONE), U4.82 (VCCIO5), U4.94 (VCCIO6), U4.103 (VCCIO6), U4.108 (VCC_ONE), U4.109 (VCC_ONE), U4.115 (VCC_ONE), U4.117 (VCCIO7), U4.128 (VCCIO8), U4.139 (VCCIO8), U4.144 (VCC_ONE); also elsewhere on the board
GND: C109.2, C110.2, C111.2, C112.2, C113.2, C114.2, C115.2, C116.2, C117.2, C118.2, C119.2, C120.2, C121.2, C122.2, C123.2, C124.2, C125.2, C126.2, C127.2, C128.2, C129.2, C130.2, C131.2, C132.2, C133.2, U4.3 (GND), U4.4 (GND), U4.42 (GND), U4.53 (GND), U4.63 (GND), U4.68 (GND), U4.83 (GND), U4.95 (GND), U4.104 (GND), U4.116 (GND), U4.125 (GND), U4.133 (GND), U4.137 (GND), U4.142 (GND), U4.PAD (GND); also elsewhere on the board
VCCA: C109.1, C112.1, C115.1, C118.1, C121.1, C124.1, FB1.2, U4.2 (VCCA), U4.5 (VCCA), U4.34 (VCCA), U4.35 (VCCA), U4.71 (VCCA), U4.107 (VCCA), U4.143 (VCCA)
